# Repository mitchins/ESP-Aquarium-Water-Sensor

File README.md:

# ESP-Aquarium-Water-Sensor

A simple water flow and quality sensor for aquariums based on ESP controller. 
This board helps measure the quality of the water and its parameteres in real-time, such that alerts and graphs can be setup.

The device is conveniently be powered off usb and provides a wifi connection for ease of connection.
The core of this device is the ubiquitous Wemos D1 Mini, which is easily available and low cost.
It has a modular list of external sensors, however if for whatever reason your application does not require it, they can be omitted.

## Features

* Measure the water flow rate (via YF-S201)
* Measure total dissolved solids (TDS) for water quality (via KS0429)
* Measure the internal water temperature (via DS18B20 probe)
* Respond to switch inputs (reed, contact or button) with 10K pull-up.
* Monitor board/enclosure/cabinet temperature and humidity (onboard DHT-11)

## Peripheral Connections

| **Component**         | **Pin**     | **Connection**    |
|-----------------------|-------------|-------------------|
| **TDS Sensor (KS0429)** | A0          | Analog output      |
| **1-Wire Sensor (DS18B20)** | D2          | 1-Wire digital protocol |
| **DHT Sensor (DHT11/DHT22)** | D4          | Digital signal     |
| **Reed Switch 1**      | D6          | Digital input      |
| **PIR Motion Sensor**  | D7          | Digital input      |
| **Water Flow Sensor (YF-S201)** | D5          | Pulse counting     |
| **Reed Switch 2**      | D8          | Digital input      |

## Software

The primary software consideration for this use case is ESPHome.
All of the functions provided are common and turnkey and thus no code is required to be written or debugged.

### ESPHome

The best way to use ESPhome is through Home Assistant, if you have that then goto the add-ons section and install it.
You can still use ESPHome manually without Home Assistant by following the latest guide [here](https://esphome.io/guides/installing_esphome.html)
### Example ESPHome Configuration:
#### Please note, this configuration is currently untested until the PCB arrives.

```YAML
esphome:
  name: aquarium_monitor
  platform: ESP8266
  board: d1_mini

wifi:
  ssid: "your_wifi_ssid"
  password: "your_wifi_password"

  # Enable fallback hotspot (captive portal) in case wifi connection fails
  ap:
    ssid: "Aquarium Monitor Fallback"
    password: "fallback_password"

captive_portal:

# Enable logging
logger:

# Enable Home Assistant API
api:
  password: "your_api_password"

# Enable over-the-air updates
ota:
  password: "your_ota_password"

# TDS Sensor (Analog Sensor)
sensor:
  - platform: adc
    pin: A0
    name: "TDS Sensor"
    update_interval: 60s

# DS18B20 Temperature Sensor (1-Wire)
dallas:
  - pin: D2

sensor:
  - platform: dallas
    address: 0xADDRESS  # Replace with actual address
    name: "Water Temperature"
    update_interval: 60s

# DHT11 Sensor (Temperature and Humidity)
dht:
  model: DHT11  # Or use DHT22 if applicable
  pin: D4
  temperature:
    name: "Air Temperature"
  humidity:
    name: "Air Humidity"
  update_interval: 60s

# YF-S201 Water Flow Sensor (Pulse Counter)
sensor:
  - platform: pulse_counter
    pin: D5
    name: "Water Flow Rate"
    unit_of_measurement: "L/min"
    update_interval: 60s

# PIR Motion Sensor (AM312 or HC-SR505)
binary_sensor:
  - platform: gpio
    pin: D7
    name: "Motion Detected"
    device_class: motion

# Reed Switch 1
binary_sensor:
  - platform: gpio
    pin: D6
    name: "Reed Switch 1"
    device_class: opening

# Reed Switch 2
binary_sensor:
  - platform: gpio
    pin: D8
    name: "Reed Switch 2"
    device_class: opening

# Optional: Status LED for debugging
status_led:
  pin:
    number: D0
    inverted: true

```

## Board Renderings

#### Front

#### Back

## Defects

| **Issue**         | **Affected**     | **Resolved**    |
|-----------------------|-------------|-------------------|
| Reversed polarity on DC Jack J3 | v1.0          | v1.1      |

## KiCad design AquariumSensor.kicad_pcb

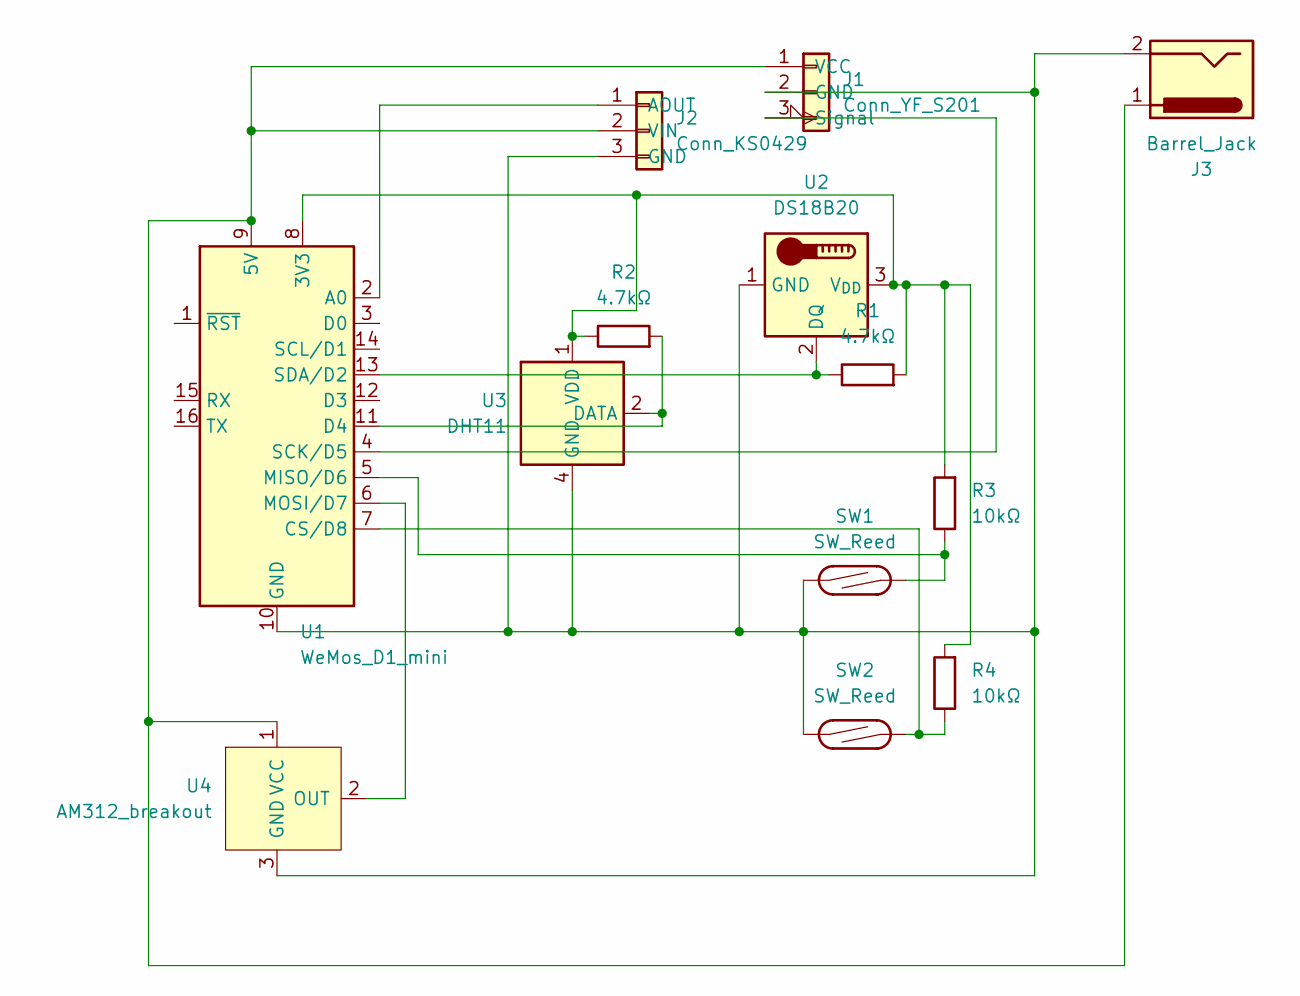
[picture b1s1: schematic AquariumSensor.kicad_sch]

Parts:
J1: Conn_YF_S201; TerminalBlock_Phoenix_MPT-0,5-3-2.54_1x03_P2.54mm_Horizontal
J2: Conn_KS0429; JST_EH_B3B-EH-A_1x03_P2.50mm_Vertical
J3: Barrel_Jack; BarrelJack_Horizontal
R1, R2: 4.7kΩ; R_Axial_DIN0207_L6.3mm_D2.5mm_P7.62mm_Horizontal
R3, R4: 10kΩ; R_Axial_DIN0207_L6.3mm_D2.5mm_P7.62mm_Horizontal
SW1, SW2: SW_Reed; TerminalBlock_Phoenix_MPT-0,5-2-2.54_1x02_P2.54mm_Horizontal
U1: WeMos_D1_mini; WEMOS_D1_mini_light
U2: DS18B20; TerminalBlock_Phoenix_MPT-0,5-3-2.54_1x03_P2.54mm_Horizontal
U3: DHT11; Aosong_DHT11_5.5x12.0_P2.54mm
U4: AM312_breakout; PinHeader_1x03_P2.54mm_Vertical

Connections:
unnamed: J1.2 (GND), J2.3 (GND), J3.2, SW1.1, SW2.1, U1.10 (GND), U2.1 (GND), U3.4 (GND), U4.3 (GND)
unnamed: J1.3 (Signal), U1.4 (SCK/D5)
unnamed: J1.1 (VCC), J2.2 (VIN), J3.1, U1.9 (5V), U4.1 (VCC)
unnamed: J2.1 (AOUT), U1.2 (A0)
unnamed: R1.2, R2.1, R3.2, R4.2, U1.8 (3V3), U2.3 (V_{DD}), U3.1 (VDD)
unnamed: R4.1, SW2.2, U1.7 (CS/D8)
unnamed: R2.2, U1.11 (D4), U3.2 (DATA)
unnamed: R3.1, SW1.2, U1.5 (MISO/D6)
unnamed: U1.6 (MOSI/D7), U4.2 (OUT)
unnamed: R1.1, U1.13 (SDA/D2), U2.2 (DQ)

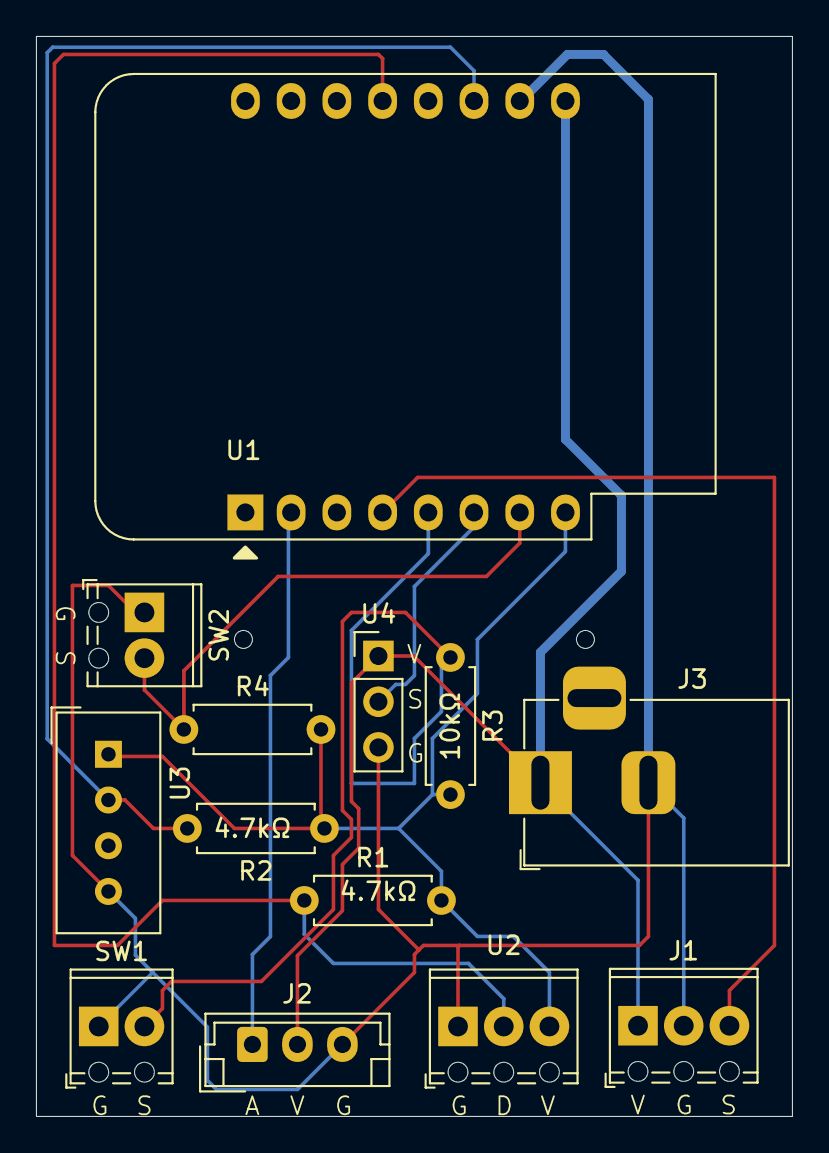
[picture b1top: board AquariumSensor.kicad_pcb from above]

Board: 2 copper layers, 42.0 x 60.0 mm, 13 parts (0 on the bottom side), 10 nets.

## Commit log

2024-10-07 Initial board prototype
2024-10-08 1.1 Release to fix wrong polarity on J3 DC Jack
2024-10-09 Update the 1.1 images and text
